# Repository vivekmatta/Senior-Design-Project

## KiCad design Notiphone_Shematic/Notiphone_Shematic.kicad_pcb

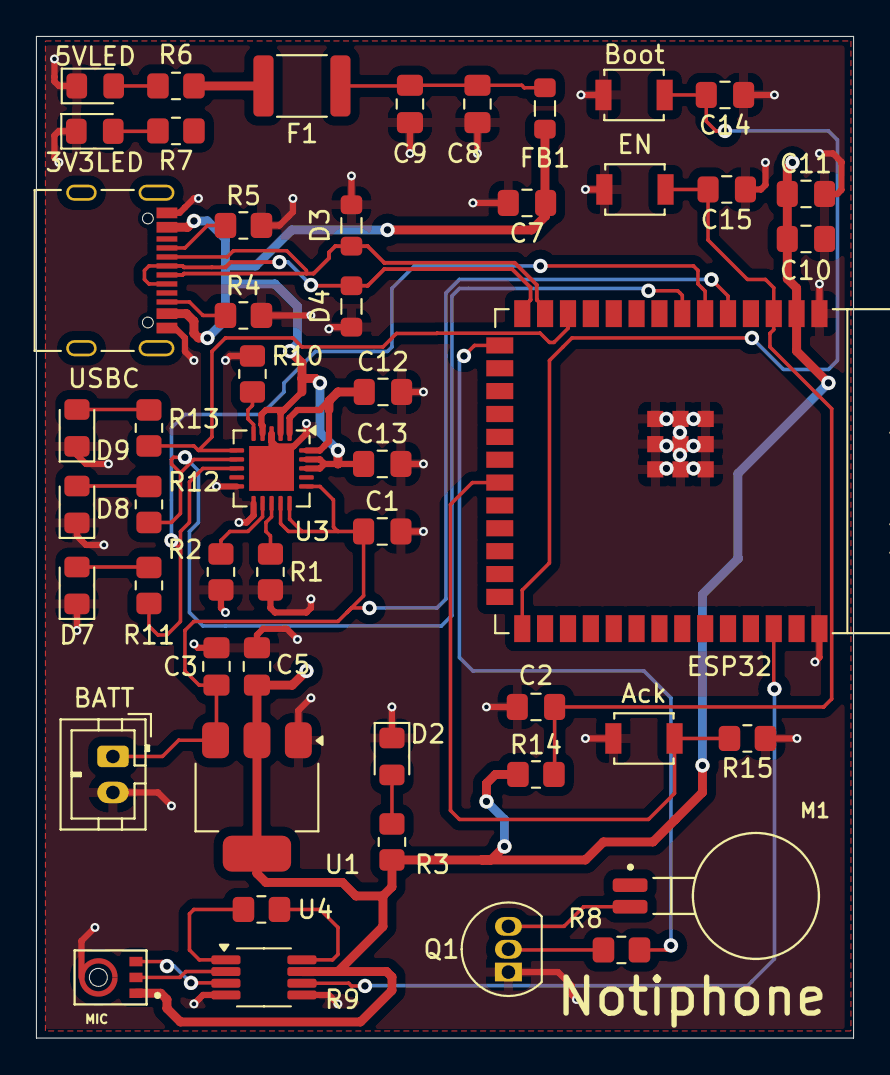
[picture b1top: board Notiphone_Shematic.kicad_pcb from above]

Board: 2 copper layers, 45.4 x 55.6 mm, 50 parts (0 on the bottom side), 34 nets.

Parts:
3V3LED, 5VLED: LED; LED_0805_2012Metric_Pad1.15x1.40mm_HandSolder
Ack: ACK_BUTTON; SW_SPST_B3U-1000P
BATT: Conn_01x02_Pin; JST_PH_B2B-PH-K_1x02_P2.00mm_Vertical
Boot: Boot; SW_SPST_B3U-1000P
C1, C9, C12, C13: 4.7u; C_0805_2012Metric_Pad1.18x1.45mm_HandSolder
C2: 1u; C_0805_2012Metric_Pad1.18x1.45mm_HandSolder
C3, C10: 10u; C_0805_2012Metric_Pad1.18x1.45mm_HandSolder
C5: 22u; C_0805_2012Metric_Pad1.18x1.45mm_HandSolder
C7: .01u; C_0805_2012Metric_Pad1.18x1.45mm_HandSolder
C8, C11, C14, C15: .1u; C_0805_2012Metric_Pad1.18x1.45mm_HandSolder
D2, D7, D8, D9: LED; LED_0805_2012Metric_Pad1.15x1.40mm_HandSolder
D3, D4: ESD9B5.0ST5G; L_0805_2012Metric_Pad1.05x1.20mm_HandSolder
EN: EN; SW_SPST_B3U-1000P
ESP32: ESP32-S3-WROOM-1
F1: 500mA; Fuse_1812_4532Metric
FB1: 120; L_0805_2012Metric_Pad1.05x1.20mm_HandSolder
M1: C0720B001F; XDCR_C0720B001F
MIC: ICS-40720; MIC_ICS-40720
Q1: 2N3904; TO-92_Inline
R1: 1k; R_0805_2012Metric_Pad1.20x1.40mm_HandSolder
R2, R9, R10, R14, R15: 10k; R_0805_2012Metric_Pad1.20x1.40mm_HandSolder
R3: 75; R_0805_2012Metric_Pad1.20x1.40mm_HandSolder
R4, R5: 5.1k; R_0805_2012Metric_Pad1.20x1.40mm_HandSolder
R6, R12: 155; R_0805_2012Metric_Pad1.20x1.40mm_HandSolder
R7: 70; R_0805_2012Metric_Pad1.20x1.40mm_HandSolder
R8, R11, R13: 150; R_0805_2012Metric_Pad1.20x1.40mm_HandSolder
U1: AMS1117-3.3; SOT-223-3_TabPin2
U3: MCP73871; QFN-20-1EP_4x4mm_P0.5mm_EP2.5x2.5mm
U4: INA333xxDGK; VSSOP-8_3x3mm_P0.65mm
USBC: USB_C_Receptacle_USB2.0_16P; USB_C_Receptacle_Palconn_UTC16-G

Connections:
+5V: F1.2, R6.1
BOOT: Boot.2, C14.2, ESP32.27 (GPIO0/BOOT)
CHRGING_LED: ESP32.6 (GPIO6/TOUCH6/ADC1_CH5), R11.1, U3.8 (STAT1/~LBO)
CHRG_COMPLETE: ESP32.7 (GPIO7/TOUCH7/ADC1_CH6), R12.1, U3.7 (STAT2)
EN: C2.1, C15.2, EN.2, ESP32.3 (EN), R14.2
GND: 3V3LED.1 (K), 5VLED.1 (K), Ack.1, BATT.2, Boot.1, C1.2, C2.2, C3.2, C5.2, C7.2, C8.2, C9.2, C10.2, C11.2, C12.2, C13.2, C14.1, C15.1, D2.1 (K), D3.1 (A1), D4.1 (A1), D7.1 (K), D8.1 (K), D9.1 (K), EN.1, ESP32.1 (GND), ESP32.40 (GND), ESP32.41 (GND), MIC.4 (GND), Q1.1 (E), R1.2, R2.2, R4.2, R5.2, R10.2, R15.1, U1.1 (GND), U3.3 (SEL), U3.10 (V_{SS}), U3.11 (V_{SS}), U3.21 (V_{SS}), U4.4 (V-), U4.5 (Ref), USBC.A1 (GND), USBC.A12 (GND), USBC.B1 (GND), USBC.B12 (GND)
GPIO_A2: ESP32.38 (GPIO2/TOUCH2/ADC1_CH1), U4.6
GPIO_A3: ESP32.15 (GPIO3/TOUCH3/ADC1_CH2), R8.1
GPIO_A5: BATT.1, C1.1, C3.1, ESP32.5 (GPIO5/TOUCH5/ADC1_CH4), U1.3 (VI), U3.14 (V_{BAT}), U3.15 (V_{BAT}), U3.16 (V_{BAT_SENSE})
GPIO_A8: ESP32.12 (GPIO8/TOUCH8/ADC1_CH7/SUBSPICS1), R13.1, U3.6 (~PG)
GPIO_A13: Ack.2, ESP32.21 (GPIO13/TOUCH13/ADC2_CH2/FSPIQ/FSPIIO7/S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), R15.2
unnamed: C8.1, C9.1, F1.1, FB1.2
unnamed: D2.2 (A), R3.2
unnamed: 5VLED.2 (A), R6.2
unnamed: 3V3LED.2 (A), R7.2
unnamed: D7.2 (A), R11.2
unnamed: D8.2 (A), R12.2
unnamed: D9.2 (A), R13.2
unnamed: R5.1, USBC.A5 (CC1)
unnamed: R4.1, USBC.B5 (CC2)
unnamed: M1.2 (V-), Q1.3 (C)
unnamed: Q1.2 (B), R8.2
unnamed: R9.1, U4.8 (Rg)
unnamed: R9.2, U4.1 (Rg)
unnamed: R1.1, U3.13 (PROG1)
unnamed: R2.1, U3.12 (PROG3)
unnamed: R10.1, U3.5 (THERM)
OUT+: MIC.3 (OUT+), U4.3 (+)
OUT-: MIC.2 (OUT-), U4.2 (-)
PWRU_IN: C7.1, C13.1, FB1.1, U3.2 (VPCC), U3.4 (PROG2), U3.18 (IN), U3.19 (IN), USBC.A4 (VBUS), USBC.A9 (VBUS), USBC.B4 (VBUS), USBC.B9 (VBUS)
USBC_D.N: D3.2 (A2), ESP32.13 (GPIO19/U1RTS/ADC2_CH8/CLK_OUT2/USB_D-), USBC.A7 (D-), USBC.B7 (D-)
USBC_D.P: D4.2 (A2), ESP32.14 (GPIO20/U1CTS/ADC2_CH9/CLK_OUT1/USB_D+), USBC.A6 (D+), USBC.B6 (D+)
VCC_3V3: C5.1, C10.1, C11.1, ESP32.2 (3V3), MIC.1 (VDD), R3.1, R14.1, U1.2 (VO), U4.7 (V+)
V_SYSTEM: C12.1, U3.1 (OUT), U3.20 (OUT)

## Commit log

2025-03-03 Updated files and worked on PCB file
2025-03-13 Updated pcb file
2025-03-13 updated code
